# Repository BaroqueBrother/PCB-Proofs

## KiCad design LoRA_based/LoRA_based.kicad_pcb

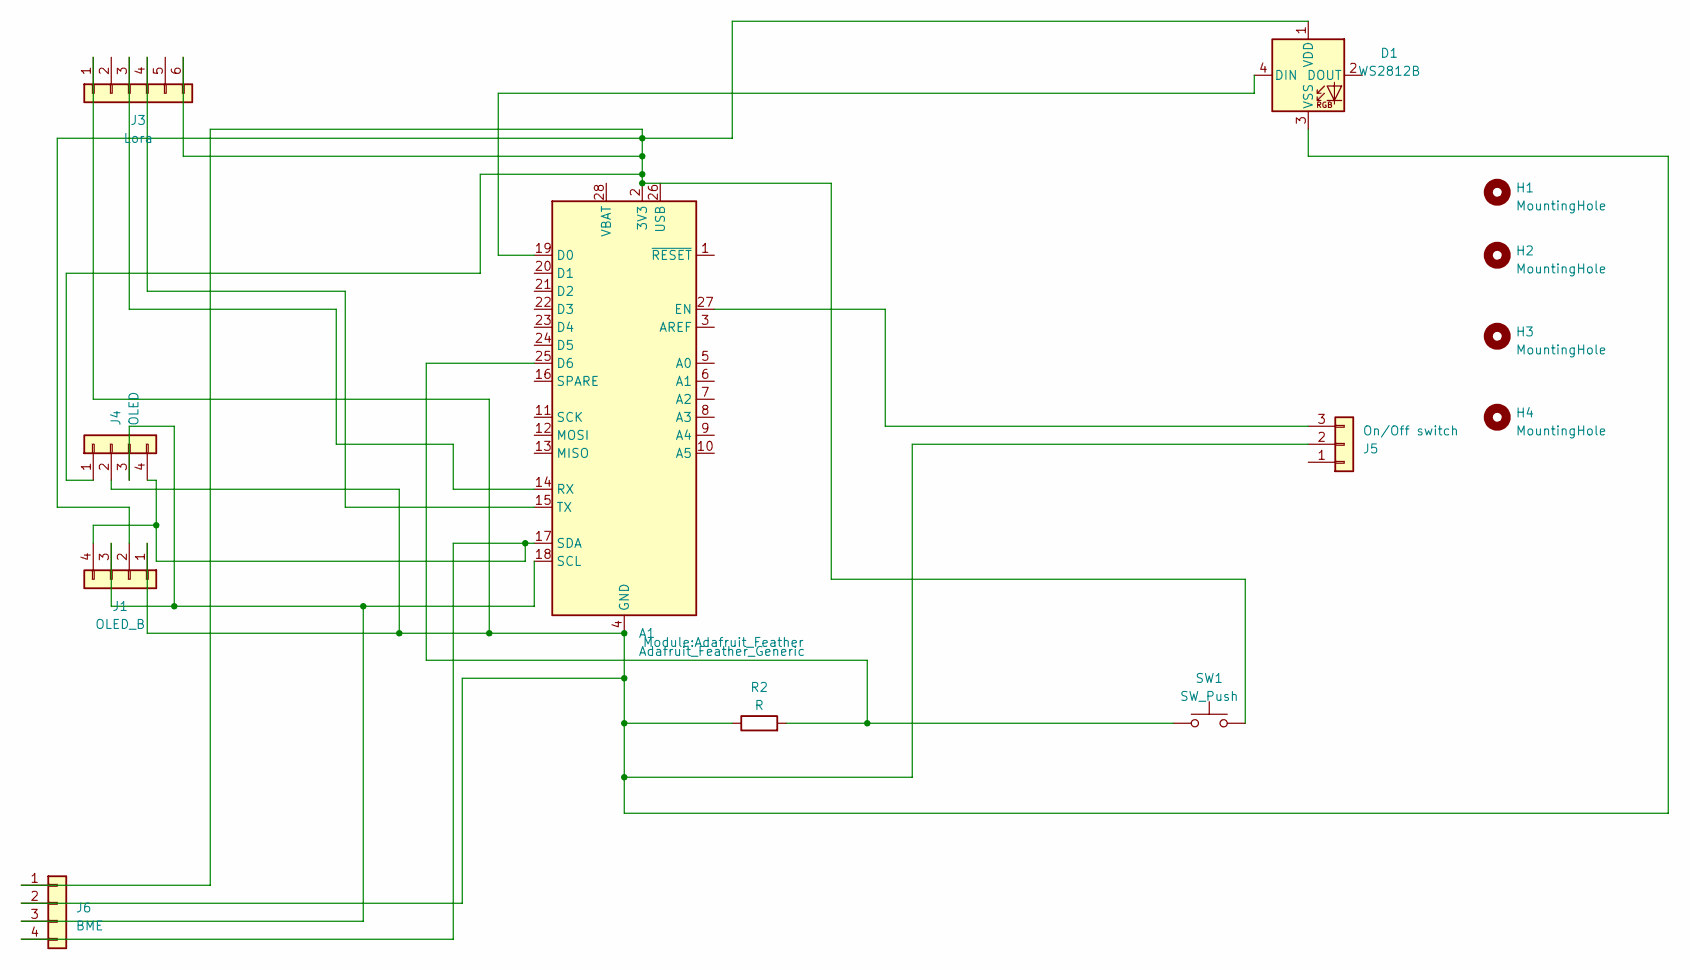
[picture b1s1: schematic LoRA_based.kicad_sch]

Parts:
A1: Adafruit_Feather_Generic; Adafruit_Feather
D1: WS2812B; LED_WS2812B_PLCC4_5.0x5.0mm_P3.2mm
H1, H2, H3, H4: MountingHole; MountingHole_3.5mm
J1: OLED_B; PinSocket_1x04_P2.54mm_Vertical
J3: Lora; PinSocket_1x06_P2.54mm_Vertical
J4: OLED; PinSocket_1x04_P2.54mm_Vertical
J5: On/Off switch; PinSocket_1x03_P2.54mm_Vertical
J6: BME; PinSocket_1x04_P2.54mm_Vertical
R2: R; R_Axial_DIN0204_L3.6mm_D1.6mm_P7.62mm_Horizontal
SW1: SW_Push; SW_PUSH_6mm

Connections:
unnamed: A1.2 (3V3), D1.1 (VDD), J1.2, J3.6, J4.1, J6.1, SW1.2
unnamed: A1.19 (D0), D1.4 (DIN)
unnamed: A1.25 (D6), R2.2, SW1.1
unnamed: A1.27 (EN), J5.3
unnamed: A1.4 (GND), D1.3 (VSS), J1.1, J3.1, J4.2, J5.2, J6.2, R2.1
unnamed: A1.14 (RX), J3.3
unnamed: A1.18 (SCL), J1.3, J4.3, J6.3
unnamed: A1.17 (SDA), J1.4, J4.4, J6.4
unnamed: A1.15 (TX), J3.4

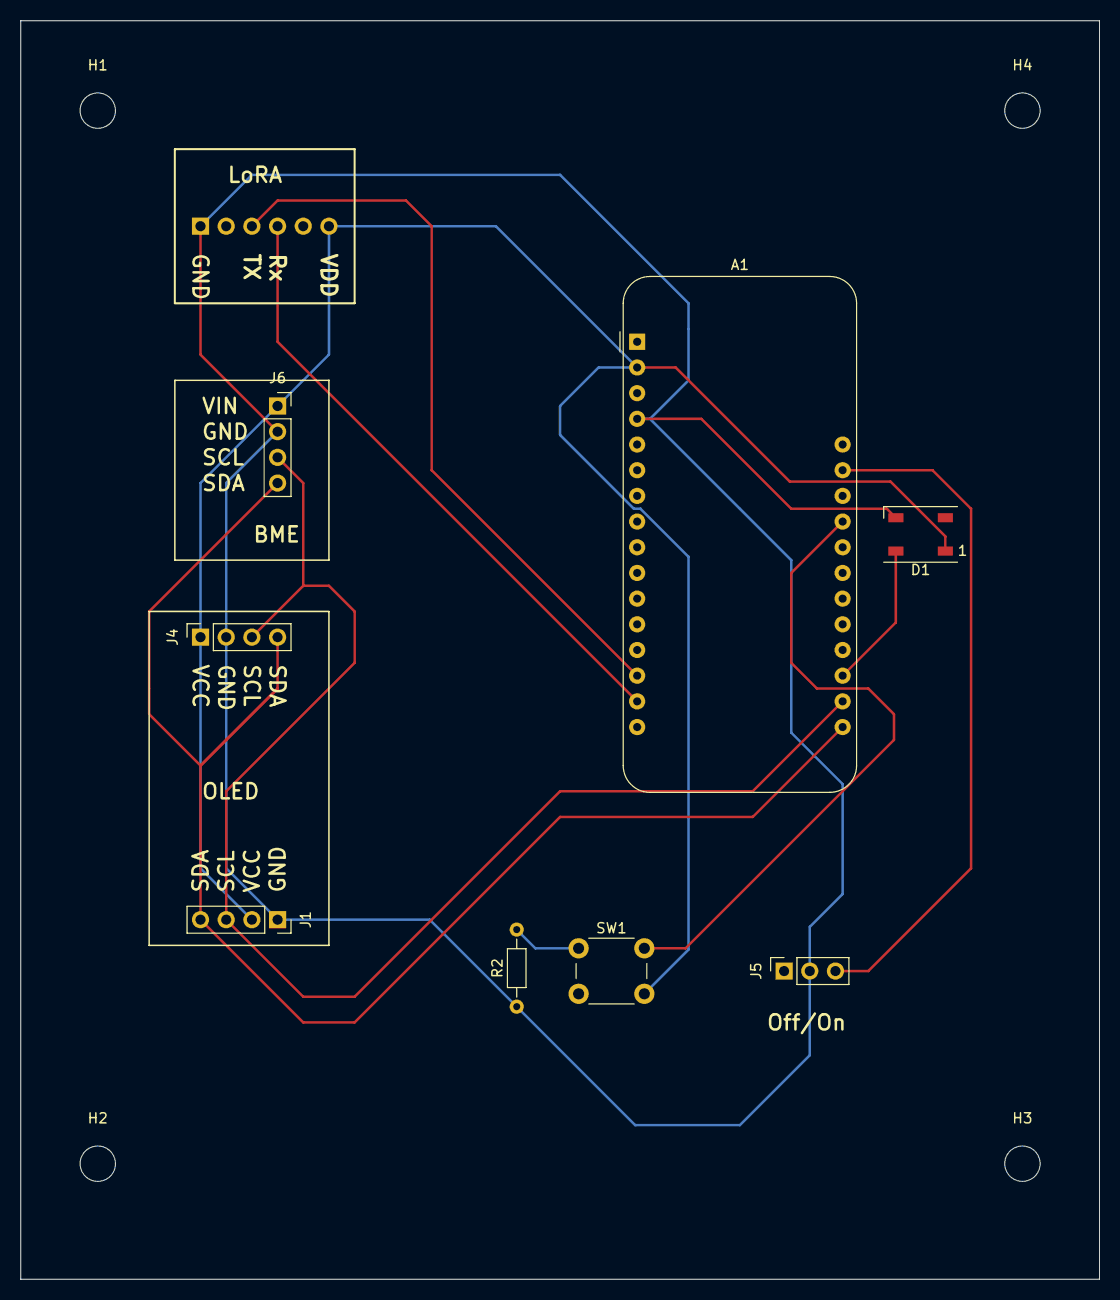
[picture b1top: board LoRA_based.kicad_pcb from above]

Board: 2 copper layers, 106.7 x 124.5 mm, 13 parts (1 on the bottom side), 9 nets.

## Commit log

2023-07-13 LoRa based PCB
